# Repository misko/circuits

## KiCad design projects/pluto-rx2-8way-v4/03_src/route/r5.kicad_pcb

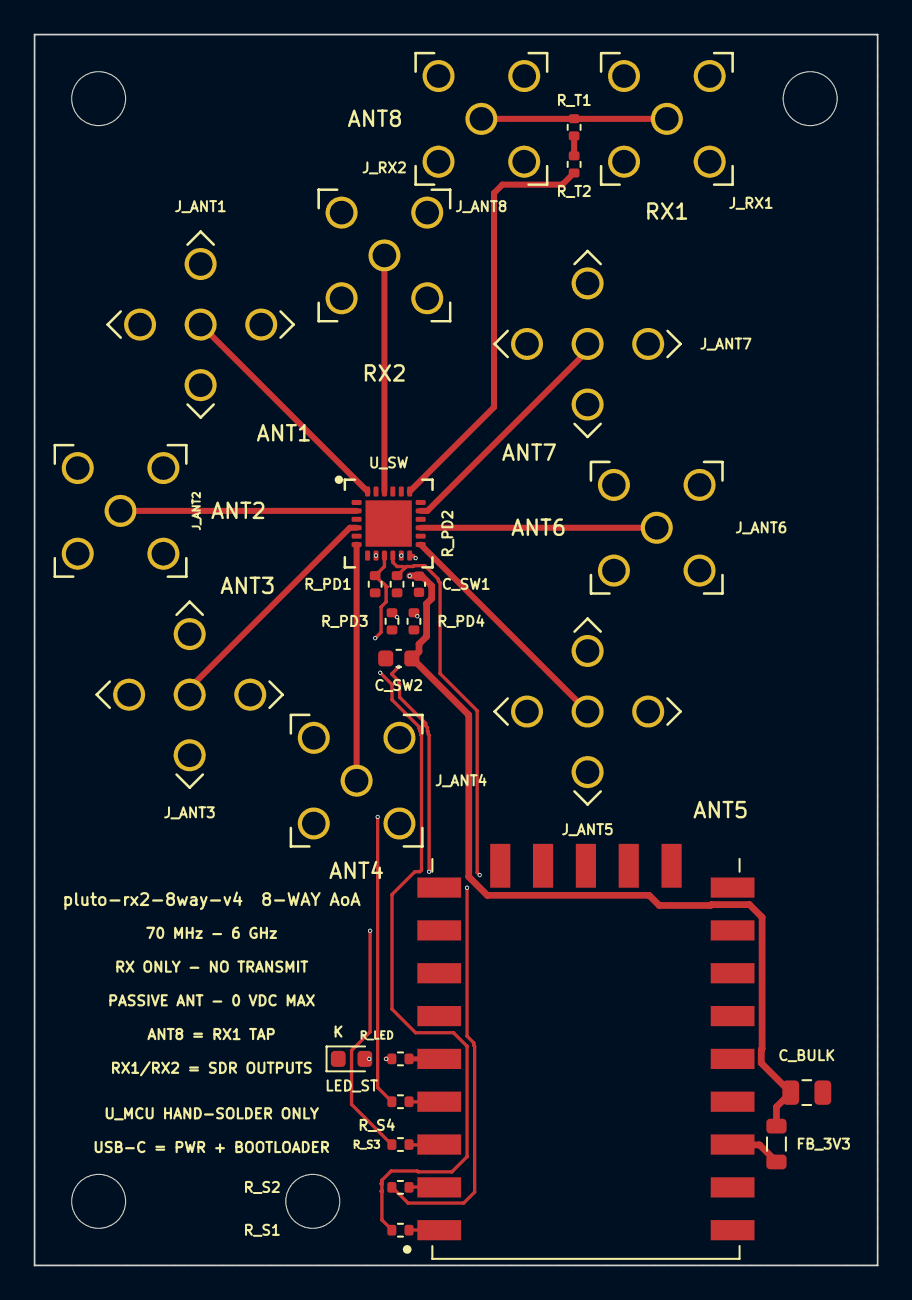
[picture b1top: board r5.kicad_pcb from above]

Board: 4 copper layers, 50.0 x 73.0 mm, 32 parts (0 on the bottom side), 24 nets.

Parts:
C_BULK: 4.7uF; C_0805_2012Metric
C_SW1: 100nF; C_0402_1005Metric
C_SW2: 1uF; C_0603_1608Metric
FB_3V3: C3716677; L_0805_2012Metric
H1, H2, H3, H4: MountingHole_3.2mm_M3
J_ANT1, J_ANT2, J_ANT3, J_ANT4, J_ANT5, J_ANT6, J_ANT7, J_ANT8: C504007; SMA_Vertical_5.08sq_D1.4
J_RX1, J_RX2: C504007; SMA_Vertical_5.08sq_D1.4
LED_ST: C2286; LED_0603_1608Metric
R_LED: 680Ω; R_0402_1005Metric
R_PD1, R_PD2, R_PD3, R_PD4: 10kΩ; R_0402_1005Metric
R_S1, R_S2, R_S3, R_S4: 100Ω; R_0402_1005Metric
R_T1, R_T2: 220Ω; R_0402_1005Metric
U_MCU: C9900173620; RP2040_Zero_LCC23_18x23.5
U_SW: C5121458; QFN-24_4x4_P0.5_EP2.7_PE42482

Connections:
3V3: C_BULK.1, C_SW1.1, C_SW2.1, FB_3V3.2, U_SW.8
3V3_MOD: FB_3V3.1, U_MCU.21
ANT1: J_ANT1.1, U_SW.24
ANT2: J_ANT2.1, U_SW.2
ANT3: J_ANT3.1, U_SW.4
ANT4: J_ANT4.1, U_SW.6
ANT5: J_ANT5.1, U_SW.13
ANT6: J_ANT6.1, U_SW.15
ANT7: J_ANT7.1, U_SW.17
GND: C_BULK.2, C_SW1.2, C_SW2.2, J_ANT1.2, J_ANT1.3, J_ANT1.4, J_ANT1.5, J_ANT2.2, J_ANT2.3, J_ANT2.4, J_ANT2.5, J_ANT3.2, J_ANT3.3, J_ANT3.4, J_ANT3.5, J_ANT4.2, J_ANT4.3, J_ANT4.4, J_ANT4.5, J_ANT5.2, J_ANT5.3, J_ANT5.4, J_ANT5.5, J_ANT6.2, J_ANT6.3, J_ANT6.4, J_ANT6.5, J_ANT7.2, J_ANT7.3, J_ANT7.4, J_ANT7.5, J_ANT8.2, J_ANT8.3, J_ANT8.4, J_ANT8.5, J_RX1.2, J_RX1.3, J_RX1.4, J_RX1.5, J_RX2.2, J_RX2.3, J_RX2.4, J_RX2.5, LED_ST.1, R_PD1.2, R_PD2.2, R_PD3.2, R_PD4.2, U_MCU.22, U_SW.1, U_SW.3, U_SW.5, U_SW.7, U_SW.14, U_SW.16, U_SW.18, U_SW.20, U_SW.21, U_SW.23, U_SW.25
LED_STAT: R_LED.1, U_MCU.5
LED_STAT_A: LED_ST.2, R_LED.2
RX1_MAIN: J_ANT8.1, J_RX1.1, R_T1.1
RX1_TAP: R_T2.2, U_SW.19
RX1_TAP_MID: R_T1.2, R_T2.1
RX2_OUT: J_RX2.1, U_SW.22
SEL_V1: R_S1.1, U_MCU.1
SEL_V2: R_S2.1, U_MCU.2
SEL_V3: R_S3.1, U_MCU.3
SEL_V4: R_S4.1, U_MCU.4
SW_V1: R_PD1.1, R_S1.2, U_SW.9
SW_V2: R_PD2.1, R_S2.2, U_SW.10
SW_V3: R_PD3.1, R_S3.2, U_SW.11
SW_V4: R_PD4.1, R_S4.2, U_SW.12

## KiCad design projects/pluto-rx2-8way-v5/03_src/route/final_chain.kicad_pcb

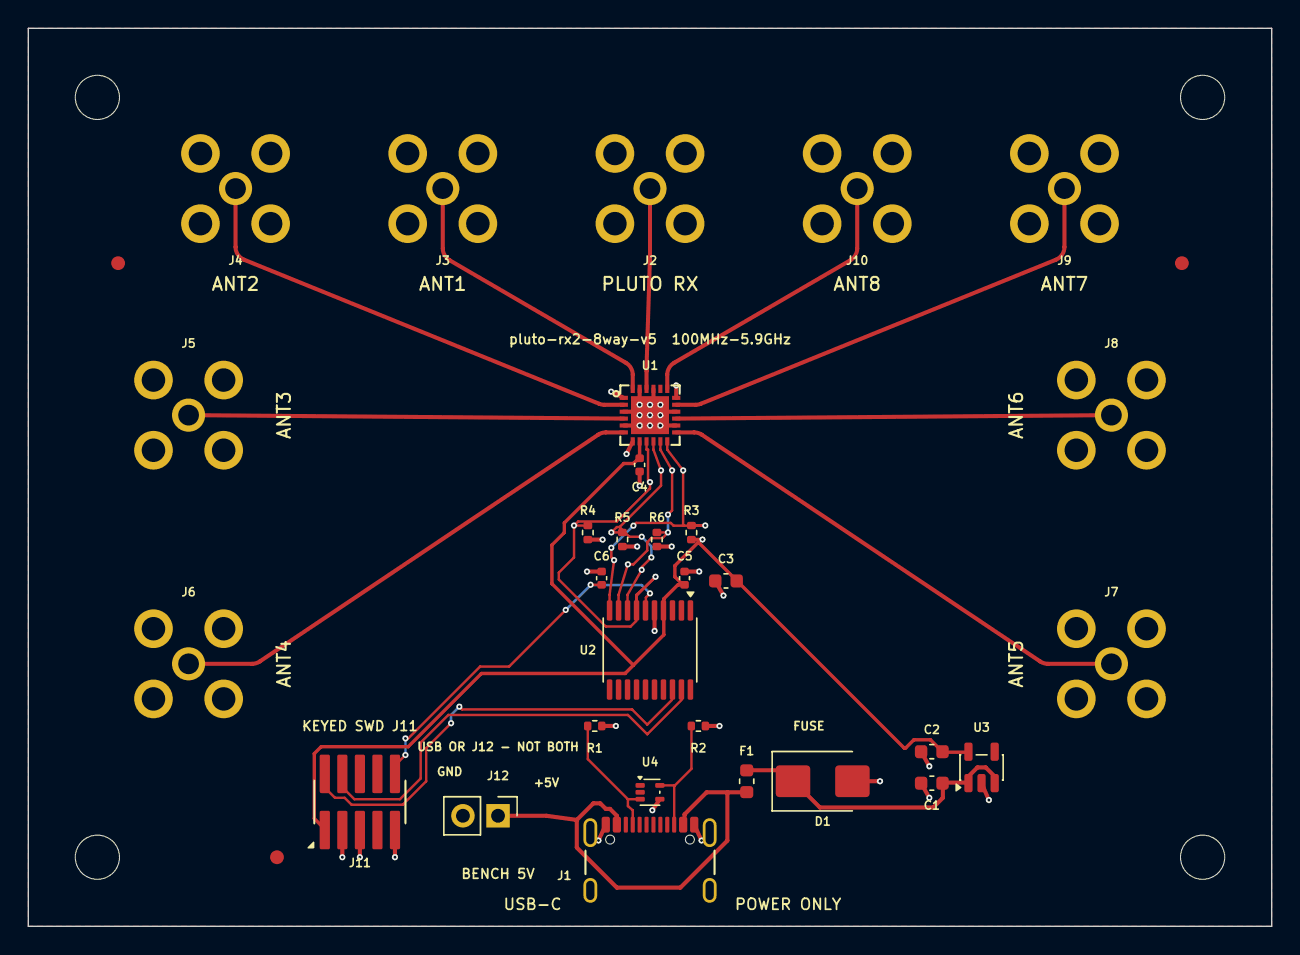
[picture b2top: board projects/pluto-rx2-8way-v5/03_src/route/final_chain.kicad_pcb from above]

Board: 4 copper layers, 90.0 x 65.0 mm, 37 parts (0 on the bottom side), 22 nets.

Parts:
C1, C2, C3: 4.7uF; C_0603_1608Metric
C4, C5, C6: 100nF; C_0402_1005Metric
D1: C83270; D_SMB
F1: C207010; Fuse_0603_1608Metric
FID1, FID2, FID3: Fiducial_1mm_Mask2mm
H1, H2, H3, H4: MountingHole_3.2mm_M3
J1: C5184243; GCT_USB4105_GF_A_120
J2, J3, J4, J5, J6, J7, J8, J9, J10: C429844; Amphenol_901_143_6RFX
J11: C2932107; Samtec_FTSH_105_01_L_DV_K_P_TR
J12: C225477; PinHeader_1x02_P2.54mm_Vertical
R1, R2: 5.1kΩ; R_0402_1005Metric
R3, R4, R5, R6: 10kΩ; R_0402_1005Metric
U1: C5121458; Psemi_PE42482_QFN24_4x4_P0.5
U2: C5452432; TSSOP-20_4.4x6.5mm_P0.65mm
U3: C2866134; SOT-23-5
U4: C1972959; SOT-553

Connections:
3V3: C2.1, C3.1, C4.1, C5.1, J11.1, R3.1, U1.8, U2.4, U3.5
GND: C1.2, C2.2, C3.2, C4.2, C5.2, C6.2, D1.2, J1.A1, J1.A12, J1.B1, J1.B12, J1.SH, J2.2, J2.3, J2.4, J2.5, J3.2, J3.3, J3.4, J3.5, J4.2, J4.3, J4.4, J4.5, J5.2, J5.3, J5.4, J5.5, J6.2, J6.3, J6.4, J6.5, J7.2, J7.3, J7.4, J7.5, J8.2, J8.3, J8.4, J8.5, J9.2, J9.3, J9.4, J9.5, J10.2, J10.3, J10.4, J10.5, J11.3, J11.5, J11.9, J12.2, R1.2, R2.2, R4.2, R5.2, R6.2, U1.1, U1.3, U1.5, U1.7, U1.14, U1.16, U1.18, U1.21, U1.23, U1.25, U2.5, U3.2, U4.4
NRST: C6.1, J11.10, U2.6
RF_ANT1: J3.1, U1.24
RF_ANT2: J4.1, U1.2
RF_ANT3: J5.1, U1.4
RF_ANT4: J6.1, U1.6
RF_ANT5: J7.1, U1.13
RF_ANT6: J8.1, U1.15
RF_ANT7: J9.1, U1.17
RF_ANT8: J10.1, U1.19
RF_COMMON: J2.1, U1.22
SWCLK: J11.4, U2.19
SWDIO: J11.2, U2.18
SW_V1: R4.1, U1.9, U2.7
SW_V2: R5.1, U1.10, U2.8
SW_V3: R6.1, U1.11, U2.9
SW_V4: R3.2, U1.12, U2.10
USB_CC1: J1.A5, R1.1, U4.3
USB_CC2: J1.B5, R2.1, U4.5
VBUS_PROTECTED: C1.1, D1.1, F1.2, U3.1, U3.3
VBUS_RAW: F1.1, J1.A4, J1.A9, J1.B4, J1.B9, J12.1

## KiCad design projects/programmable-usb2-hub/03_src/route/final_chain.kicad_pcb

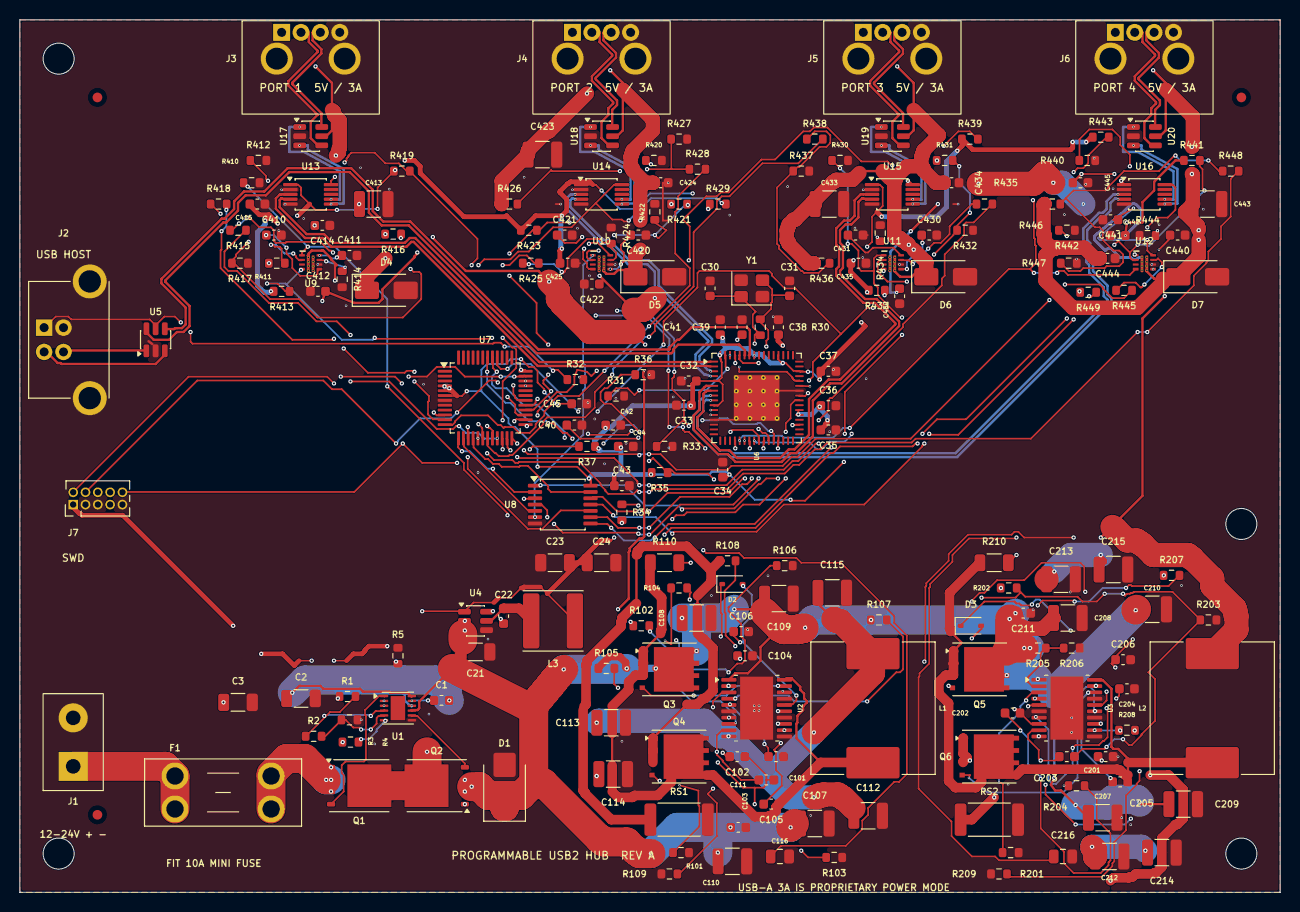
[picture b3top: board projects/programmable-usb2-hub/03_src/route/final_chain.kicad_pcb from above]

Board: 4 copper layers, 130.0 x 90.0 mm, 206 parts (0 on the bottom side), 145 nets.

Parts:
C1: 220nF; C_0603_1608Metric
C2, C3: 100nF; C_1206_3216Metric
C21: 10uF; C_1206_3216Metric
C22, C32, C33, C34, C35, C38, C39, C42, C44, C45, C111, C211, C412, C414, C415, C422, C424, C425, C432, C434, C435, C442, C444, C445: 100nF; C_0603_1608Metric
C23, C24: 22uF; C_1206_3216Metric
C30, C31: 18pF; C_0603_1608Metric
C36, C37, C40, C41, C105, C106, C205, C206: 1uF; C_0603_1608Metric
C43: 4.7uF; C_0603_1608Metric
C101, C201: 330pF; C_0603_1608Metric
C102, C202, C410, C420, C430, C440: 3.3nF; C_0603_1608Metric
C103, C203: 100pF; C_0603_1608Metric
C104, C204: 10nF; C_0603_1608Metric
C107, C108, C109, C110, C207, C208, C209, C210: 10uF; C_1210_3225Metric
C112, C113, C114, C115, C212, C213, C214, C215: 100uF; C_1210_3225Metric
C116, C216: 1nF; C_0805_2012Metric
C411, C421, C431, C441: 2.2nF; C_0603_1608Metric
C413, C423, C433, C443: 22uF; C_1210_3225Metric
D1: C315992; D_SMB
D2, D3: C2128; D_SOD-323
D4, D5, D6, D7: C85098; D_SMA
F1: C5249699; Fuseholder_Blade_Mini_Keystone_3568
FID1, FID2, FID3: Fiducial_1mm_Mask2mm
H1, H2, H3, H4: MountingHole_3.2mm_M3
J1: C8404; TerminalBlock_KANGNEX_WJ126V_2P_P5.0
J2: C86462; USB_B_TE_292304-1_Horizontal
J3, J4, J5, J6: USB1130-15-A; USB_A_GCT_USB1130_Horizontal
J7: C19191796; PinHeader_2x05_P1.27mm_Vertical
L1, L2: C408523; L_Sunlord_MWSA1206S-6R8
L3: C266428; L_Sunlord_SWPA6028S
Q1, Q2: C454269; TDSON-8-1
Q3, Q4, Q5, Q6: C404363; PowerPAK_SO-8_Single_Paste65
R1: 88.7kΩ; R_0603_1608Metric
R2, R108, R109, R208, R209: 0Ω; R_0603_1608Metric
R3: 4.75kΩ; R_0603_1608Metric
R4: 90.9kΩ; R_0603_1608Metric
R5: 11.5kΩ; R_0603_1608Metric
R30: 1MΩ; R_0603_1608Metric
R31: 12kΩ; R_0603_1608Metric
R32, R33, R107, R207, R410, R416, R420, R426, R430, R436, R440, R446: 100kΩ; R_0603_1608Metric
R34, R35: 4.7kΩ; R_0603_1608Metric
R36, R37, R412, R413, R419, R422, R423, R429, R432, R433, R439, R442, R443, R449: 10kΩ; R_0603_1608Metric
R101, R201: 12.4kΩ; R_0603_1608Metric
R102, R202: 3.92kΩ; R_0603_1608Metric
R103, R203: 1.21kΩ; R_0603_1608Metric
R104, R204: 18kΩ; R_0603_1608Metric
R105, R205: 49.9kΩ; R_0603_1608Metric
R106, R206: 6.98kΩ; R_0603_1608Metric
R110, R210: 2.2Ω; R_1206_3216Metric
R411, R421, R431, R441: 36.5kΩ; R_0603_1608Metric
R414, R424, R434, R444: 976Ω; R_0603_1608Metric
R415, R418, R425, R428, R435, R438, R445, R448: 1kΩ; R_0603_1608Metric
R417, R427, R437, R447: 68kΩ; R_0603_1608Metric
RS1, RS2: 10mΩ; R_2512_6332Metric
U1: C3215601; WSON-12-1EP_3x3mm_P0.5mm_EP1.5x2.5mm
U2, U3: C13755; HTSSOP-20-1EP_4.4x6.5mm_P0.65mm_EP3.4x6.5mm_Mask2.75x3.43mm
U4: C780769; TSOT-23-6
U5, U17, U18, U19, U20: C7519; SOT-23-6
U6: C478081; QFN-64-1EP_9x9mm_P0.5mm_EP4.7x4.7mm_ThermalVias
U7: C2847904; LQFP-48_7x7mm_P0.5mm
U8: C6053; TSSOP-14_4.4x5mm_P0.65mm
U9, U10, U11, U12: C3662799; Texas_RPW0010A_VQFN-HR-10_2x2mm_P0.45mm_ThermalVias
U13, U14, U15, U16: C11355; MSOP-10_3x3mm_P0.5mm
Y1: C1985204; Crystal_SMD_3225-4Pin_3.2x2.5mm

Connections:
3V3_LOGIC: C23.1, C24.1, C32.1, C33.1, C34.1, C35.1, C36.1, C37.1, C38.1, C39.1, C42.1, C43.1, C44.1, C45.1, C415.1, C425.1, C435.1, C445.1, J7.1, L3.2, R34.1, R35.1, R37.2, R413.1, R419.1, R423.1, R429.1, R433.1, R439.1, R443.1, R449.1, U4.1, U6.5, U6.10, U6.24, U6.35, U6.37, U6.38, U6.46, U6.52, U6.57, U6.64, U7.4, U7.5, U7.6, U8.14, U13.1, U14.1, U15.1, U16.1
5V_A: C112.1, C113.1, C114.1, C115.1, C412.1, C422.1, L1.2, R102.1, R411.1, R421.1, U2.10, U9.5, U10.5
5V_B: C212.1, C213.1, C214.1, C215.1, C432.1, C442.1, L2.2, R202.1, R431.1, R441.1, U3.10, U11.5, U12.5
ADC_P1_IMON: R415.2, U7.21
ADC_P1_VBUS: R418.2, U7.11
ADC_P2_IMON: R425.2, U7.22
ADC_P2_VBUS: R428.2, U7.12
ADC_P3_IMON: R435.2, U7.23
ADC_P3_VBUS: R438.2, U7.19
ADC_P4_IMON: R445.2, U7.24
ADC_P4_VBUS: R448.2, U7.20
BOOT_A: C105.1, D2.1, U2.18
BOOT_B: C205.1, D3.1, U3.18
BST_3V3: C22.1, U4.6
CAP: C1.1, U1.11
CMZ_A: C102.1, R104.2
CMZ_B: C202.1, R204.2
COMP_A: C103.1, R104.1, U2.9
COMP_B: C203.1, R204.1, U3.9
CSF_A: R108.2, U2.12
CSF_B: R208.2, U3.12
CSGF_A: R109.2, U2.13
CSGF_B: R209.2, U3.13
CS_A: Q4.1, Q4.2, Q4.3, R108.1, RS1.1
CS_B: Q6.1, Q6.2, Q6.3, R208.1, RS2.1
DGATE: Q1.4, U1.1
EN_A: R107.2, U2.4
EN_B: R207.2, U3.4
FB_A: C102.2, C103.2, R102.2, R103.1, U2.8
FB_B: C202.2, C203.2, R202.2, R203.1, U3.8
FET_MID: C1.2, C2.1, Q1.5, Q2.5, U1.10, U1.12
GND: C2.2, C3.2, C21.2, C23.2, C24.2, C30.2, C31.2, C32.2, C33.2, C34.2, C35.2, C36.2, C37.2, C38.2, C39.2, C40.2, C41.2, C42.2, C43.2, C44.2, C45.2, C101.2, C104.2, C106.2, C107.2, C108.2, C109.2, C110.2, C111.2, C112.2, C113.2, C114.2, C115.2, C116.2, C201.2, C204.2, C206.2, C207.2, C208.2, C209.2, C210.2, C211.2, C212.2, C213.2, C214.2, C215.2, C216.2, C410.2, C411.2, C412.2, C413.2, C414.2, C415.2, C420.2, C421.2, C422.2, C423.2, C424.2, C425.2, C430.2, C431.2, C432.2, C433.2, C434.2, C435.2, C440.2, C441.2, C442.2, C443.2, C444.2, C445.2, D1.2, D4.2, D5.2, D6.2, D7.2, J1.2, J2.4, J2.5, J3.4, J3.5, J4.4, J4.5, J5.4, J5.5, J6.4, J6.5, J7.3, J7.5, J7.9, R3.2, R5.2, R31.2, R33.2, R36.2, R101.2, R103.2, R106.2, R109.1, R201.2, R203.2, R206.2, R209.1, R410.2, R412.2, R414.2, R417.2, R420.2, R422.2, R424.2, R427.2, R430.2, R432.2, R434.2, R437.2, R440.2, R442.2, R444.2, R447.2, RS1.2, RS2.2, U1.7, U2.6, U2.11, U2.14, U2.17, U2.21, U3.6, U3.11, U3.14, U3.17, U3.21, U4.4, U5.2, U6.13, U6.42, U6.65, U7.7, U8.7, U9.8, U10.8, U11.8, U12.8, U13.2, U13.5, U14.2, U14.5, U15.2, U15.5, U16.2, U16.5, U17.2, U18.2, U19.2, U20.2, Y1.2, Y1.4
HGATE: Q2.4, U1.8
HO_A: Q3.4, U2.19
HO_B: Q5.4, U3.19
HUB_PP1: U6.29, U8.1
HUB_PP2: U6.26, U8.4
HUB_PP3: U6.23, U8.9
HUB_PP4: U6.20, U8.12
HUB_RESET_N: R36.1, U6.43, U7.42
HUB_SCL: R35.2, U6.41, U7.40
HUB_SDA: R34.2, U6.40, U7.41
HUB_VBUS_DET: R32.2, R33.1, U6.44
LO_A: Q4.4, U2.15
LO_B: Q6.4, U3.15
MCU_NRST: J7.10, R37.1, U7.10
MGMT_N: U6.11, U7.33
MGMT_P: U6.12, U7.34
OV_SENSE: R2.2, R3.1, U1.5
OV_TOP: R1.2, R2.1, U1.4
P1_CONN_N: J3.2, U17.4
P1_CONN_P: J3.3, U17.6
P1_DATA_ISO: R419.2, U7.17, U13.10
P1_DVDT: C410.1, U9.7
P1_FLT_N: R413.2, U6.28, U7.27, U9.4
P1_HUB_N: U6.1, U13.4
P1_HUB_P: U6.2, U13.3
P1_ILIM: R414.1, R415.1, U9.9
P1_ITIMER: C411.1, U9.10
P1_OVLO: R411.2, R412.1, U9.2
P1_PORT_N: U13.6, U17.3
P1_PORT_P: U13.7, U17.1
P1_PWR_CMD: U7.13, U8.2
P1_PWR_EN: R410.1, U8.3, U9.1
P1_VBUS: C413.1, C414.1, D4.1, J3.1, R416.1, U9.6, U17.5
P1_VBUS_SENSE: R416.2, R417.1, R418.1
P2_CONN_N: J4.2, U18.4
P2_CONN_P: J4.3, U18.6
P2_DATA_ISO: R429.2, U7.18, U14.10
P2_DVDT: C420.1, U10.7
P2_FLT_N: R423.2, U6.27, U7.28, U10.4
P2_HUB_N: U6.3, U14.4
P2_HUB_P: U6.4, U14.3
P2_ILIM: R424.1, R425.1, U10.9
P2_ITIMER: C421.1, U10.10
P2_OVLO: R421.2, R422.1, U10.2
P2_PORT_N: U14.6, U18.3
P2_PORT_P: U14.7, U18.1
P2_PWR_CMD: U7.14, U8.5
P2_PWR_EN: R420.1, U8.6, U10.1
P2_VBUS: C423.1, C424.1, D5.1, J4.1, R426.1, U10.6, U18.5
P2_VBUS_SENSE: R426.2, R427.1, R428.1
P3_CONN_N: J5.2, U19.4
P3_CONN_P: J5.3, U19.6
P3_DATA_ISO: R439.2, U7.25, U15.10
P3_DVDT: C430.1, U11.7
P3_FLT_N: R433.2, U6.22, U7.29, U11.4
P3_HUB_N: U6.6, U15.4
P3_HUB_P: U6.7, U15.3
P3_ILIM: R434.1, R435.1, U11.9
P3_ITIMER: C431.1, U11.10
P3_OVLO: R431.2, R432.1, U11.2
P3_PORT_N: U15.6, U19.3
P3_PORT_P: U15.7, U19.1
P3_PWR_CMD: U7.15, U8.10
P3_PWR_EN: R430.1, U8.8, U11.1
P3_VBUS: C433.1, C434.1, D6.1, J5.1, R436.1, U11.6, U19.5
P3_VBUS_SENSE: R436.2, R437.1, R438.1
P4_CONN_N: J6.2, U20.4
P4_CONN_P: J6.3, U20.6
P4_DATA_ISO: R449.2, U7.26, U16.10
P4_DVDT: C440.1, U12.7
P4_FLT_N: R443.2, U6.21, U7.30, U12.4
P4_HUB_N: U6.8, U16.4
P4_HUB_P: U6.9, U16.3
P4_ILIM: R444.1, R445.1, U12.9
P4_ITIMER: C441.1, U12.10
P4_OVLO: R441.2, R442.1, U12.2
P4_PORT_N: U16.6, U20.3
P4_PORT_P: U16.7, U20.1
P4_PWR_CMD: U7.16, U8.13
P4_PWR_EN: R440.1, U8.11, U12.1
P4_VBUS: C443.1, C444.1, D7.1, J6.1, R446.1, U12.6, U20.5
P4_VBUS_SENSE: R446.2, R447.1, R448.1
RAMP_A: C101.1, U2.5
RAMP_B: C201.1, U3.5
RBIAS: R31.1, U6.63
RT_A: R101.1, U2.3
RT_B: R201.1, U3.3
SNUB_A: C116.1, R110.2
SNUB_B: C216.1, R210.2
SS_A: C104.1, U2.7
SS_B: C204.1, U3.7
SWCLK: J7.4, U7.36
SWDIO: J7.2, U7.35
SW_3V3: C22.2, L3.1, U4.5
SW_A: C105.2, L1.1, Q3.1, Q3.2, Q3.3, Q4.5, R110.1, U2.20
SW_B: C205.2, L2.1, Q5.1, Q5.2, Q5.3, Q6.5, R210.1, U3.20
UP_CONN_N: J2.2, U5.3
UP_CONN_P: J2.3, U5.1
UP_HUB_N: U5.4, U6.58
UP_HUB_P: U5.6, U6.59
USB_UP_VBUS: J2.1, R32.1, U5.5
UVLO_A: R105.2, R106.1, U2.2
UVLO_B: R205.2, R206.1, U3.2
UV_SENSE: R4.2, R5.1, U1.6
VCC_A: C106.1, D2.2, U2.16
VCC_B: C206.1, D3.2, U3.16
VDD18: C40.1, U6.25
VDD18PLL: C41.1, U6.62
VIN_FUSED: C3.1, F1.2, Q1.1, Q1.2, Q1.3, R1.1, R4.1, U1.2, U1.3
VIN_PROTECTED: C21.1, C107.1, C108.1, C109.1, C110.1, C111.1, C207.1, C208.1, C209.1, C210.1, C211.1, D1.1, Q2.1, Q2.2, Q2.3, Q3.5, Q5.5, R105.1, R107.1, R205.1, R207.1, U1.9, U2.1, U3.1, U4.2, U4.3
VIN_RAW: F1.1, J1.1
XTAL1: C30.1, R30.1, U6.61, Y1.1
XTAL2: C31.1, R30.2, U6.60, Y1.3
